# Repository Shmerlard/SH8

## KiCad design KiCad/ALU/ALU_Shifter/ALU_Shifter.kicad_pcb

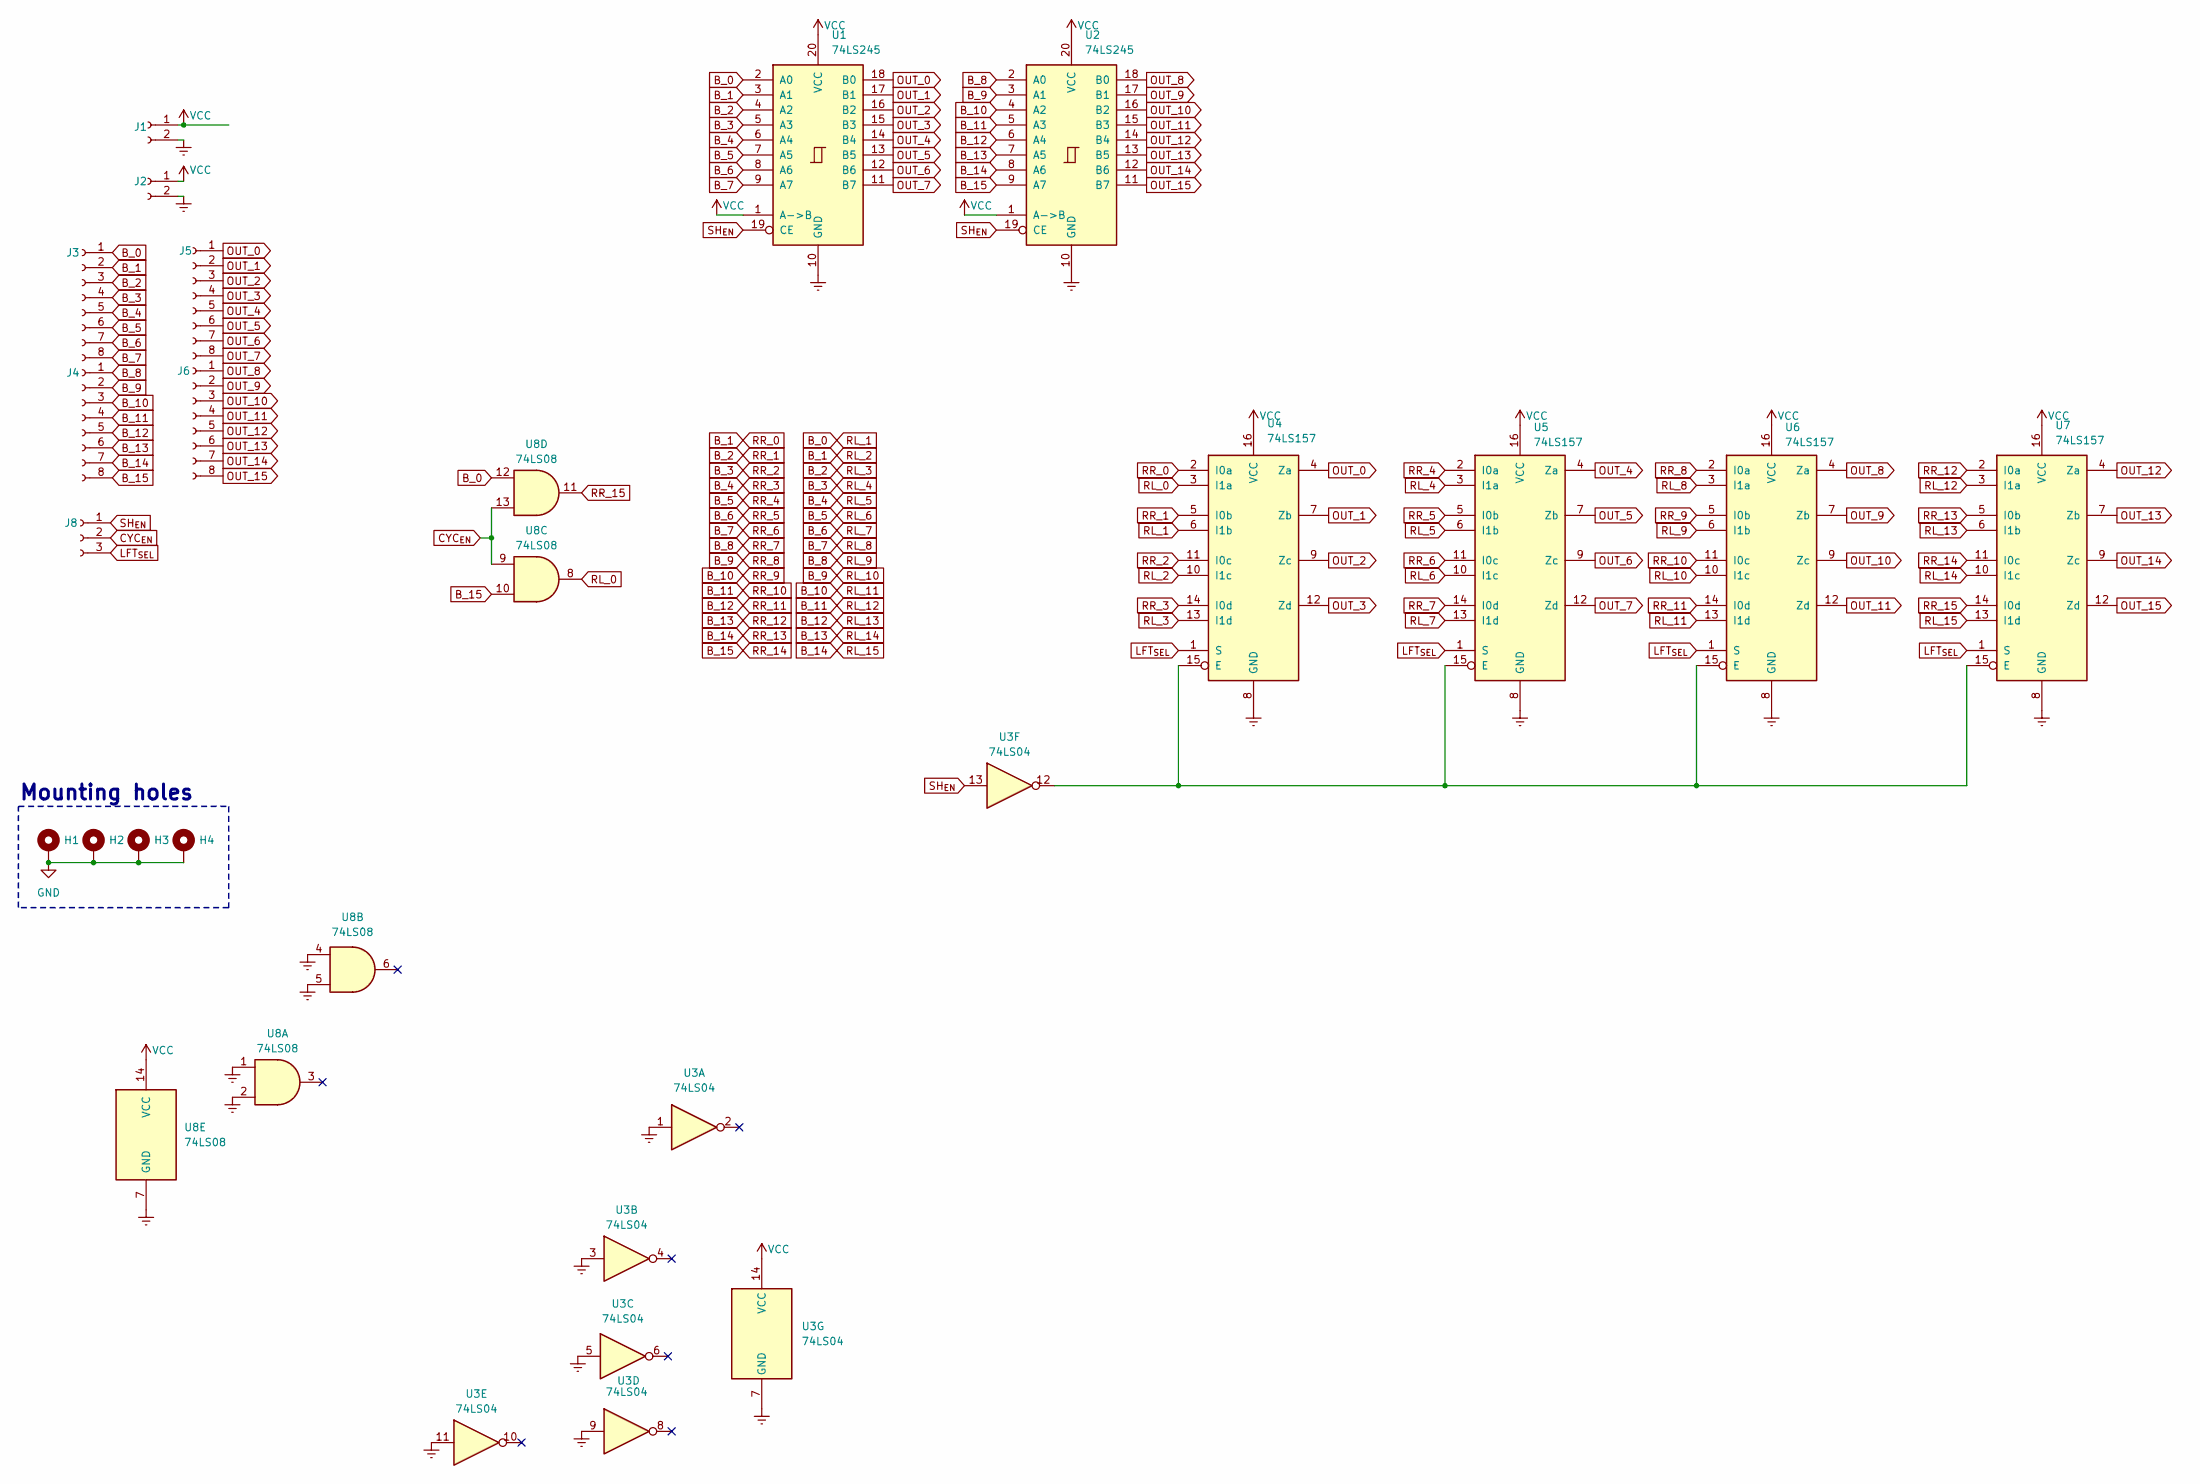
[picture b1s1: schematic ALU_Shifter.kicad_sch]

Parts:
H1, H2, H3, H4: MountingHole_Pad; MountingHole_2.2mm_M2_DIN965_Pad
J1, J2: Conn_01x02_Socket; JST_XH_S2B-XH-A-1_1x02_P2.50mm_Horizontal
J3, J4, J5, J6: Conn_01x08_Socket; jst_xh_s8b_smd
J8: Conn_01x03_Socket; JST_XH_S3B-XH-A-1_1x03_P2.50mm_Horizontal
U1, U2: 74LS245; DIP-20_W7.62mm_Socket_LongPads
U3: 74LS04; DIP-14_W7.62mm_Socket_LongPads
U4, U5, U6, U7: 74LS157; DIP-16_W7.62mm_Socket_LongPads
U8: 74LS08; DIP-14_W7.62mm_Socket_LongPads

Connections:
B_0: J3.1, U1.2 (A0), U4.6 (I1b), U8.12
B_1: J3.2, U1.3 (A1), U4.2 (I0a), U4.10 (I1c)
B_2: J3.3, U1.4 (A2), U4.5 (I0b), U4.13 (I1d)
B_3: J3.4, U1.5 (A3), U4.11 (I0c), U5.3 (I1a)
B_4: J3.5, U1.6 (A4), U4.14 (I0d), U5.6 (I1b)
B_5: J3.6, U1.7 (A5), U5.2 (I0a), U5.10 (I1c)
B_6: J3.7, U1.8 (A6), U5.5 (I0b), U5.13 (I1d)
B_7: J3.8, U1.9 (A7), U5.11 (I0c), U6.3 (I1a)
B_8: J4.1, U2.2 (A0), U5.14 (I0d), U6.6 (I1b)
B_9: J4.2, U2.3 (A1), U6.2 (I0a), U6.10 (I1c)
B_10: J4.3, U2.4 (A2), U6.5 (I0b), U6.13 (I1d)
B_11: J4.4, U2.5 (A3), U6.11 (I0c), U7.3 (I1a)
B_12: J4.5, U2.6 (A4), U6.14 (I0d), U7.6 (I1b)
B_13: J4.6, U2.7 (A5), U7.2 (I0a), U7.10 (I1c)
B_14: J4.7, U2.8 (A6), U7.5 (I0b), U7.13 (I1d)
B_15: J4.8, U2.9 (A7), U7.11 (I0c), U8.10
CYC_{EN}: J8.2, U8.9, U8.13
GND: H1.1, H2.1, H3.1, H4.1, J1.2, J2.2, U1.10 (GND), U2.10 (GND), U3.1, U3.3, U3.5, U3.7 (GND), U3.9, U3.11, U4.8 (GND), U5.8 (GND), U6.8 (GND), U7.8 (GND), U8.1, U8.2, U8.4, U8.5, U8.7 (GND)
LFT_{SEL}: J8.3, U4.1 (S), U5.1 (S), U6.1 (S), U7.1 (S)
unnamed: U3.12, U4.15 (E), U5.15 (E), U6.15 (E), U7.15 (E)
OUT_0: J5.1, U1.18 (B0), U4.4 (Za)
OUT_1: J5.2, U1.17 (B1), U4.7 (Zb)
OUT_2: J5.3, U1.16 (B2), U4.9 (Zc)
OUT_3: J5.4, U1.15 (B3), U4.12 (Zd)
OUT_4: J5.5, U1.14 (B4), U5.4 (Za)
OUT_5: J5.6, U1.13 (B5), U5.7 (Zb)
OUT_6: J5.7, U1.12 (B6), U5.9 (Zc)
OUT_7: J5.8, U1.11 (B7), U5.12 (Zd)
OUT_8: J6.1, U2.18 (B0), U6.4 (Za)
OUT_9: J6.2, U2.17 (B1), U6.7 (Zb)
OUT_10: J6.3, U2.16 (B2), U6.9 (Zc)
OUT_11: J6.4, U2.15 (B3), U6.12 (Zd)
OUT_12: J6.5, U2.14 (B4), U7.4 (Za)
OUT_13: J6.6, U2.13 (B5), U7.7 (Zb)
OUT_14: J6.7, U2.12 (B6), U7.9 (Zc)
OUT_15: J6.8, U2.11 (B7), U7.12 (Zd)
RL_0: U4.3 (I1a), U8.8
RR_15: U7.14 (I0d), U8.11
SH_{EN}: J8.1, U1.19 (CE), U2.19 (CE), U3.13
VCC: J1.1, J2.1, U1.1 (A->B), U1.20 (VCC), U2.1 (A->B), U2.20 (VCC), U3.14 (VCC), U4.16 (VCC), U5.16 (VCC), U6.16 (VCC), U7.16 (VCC), U8.14 (VCC)

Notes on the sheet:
Mounting holes

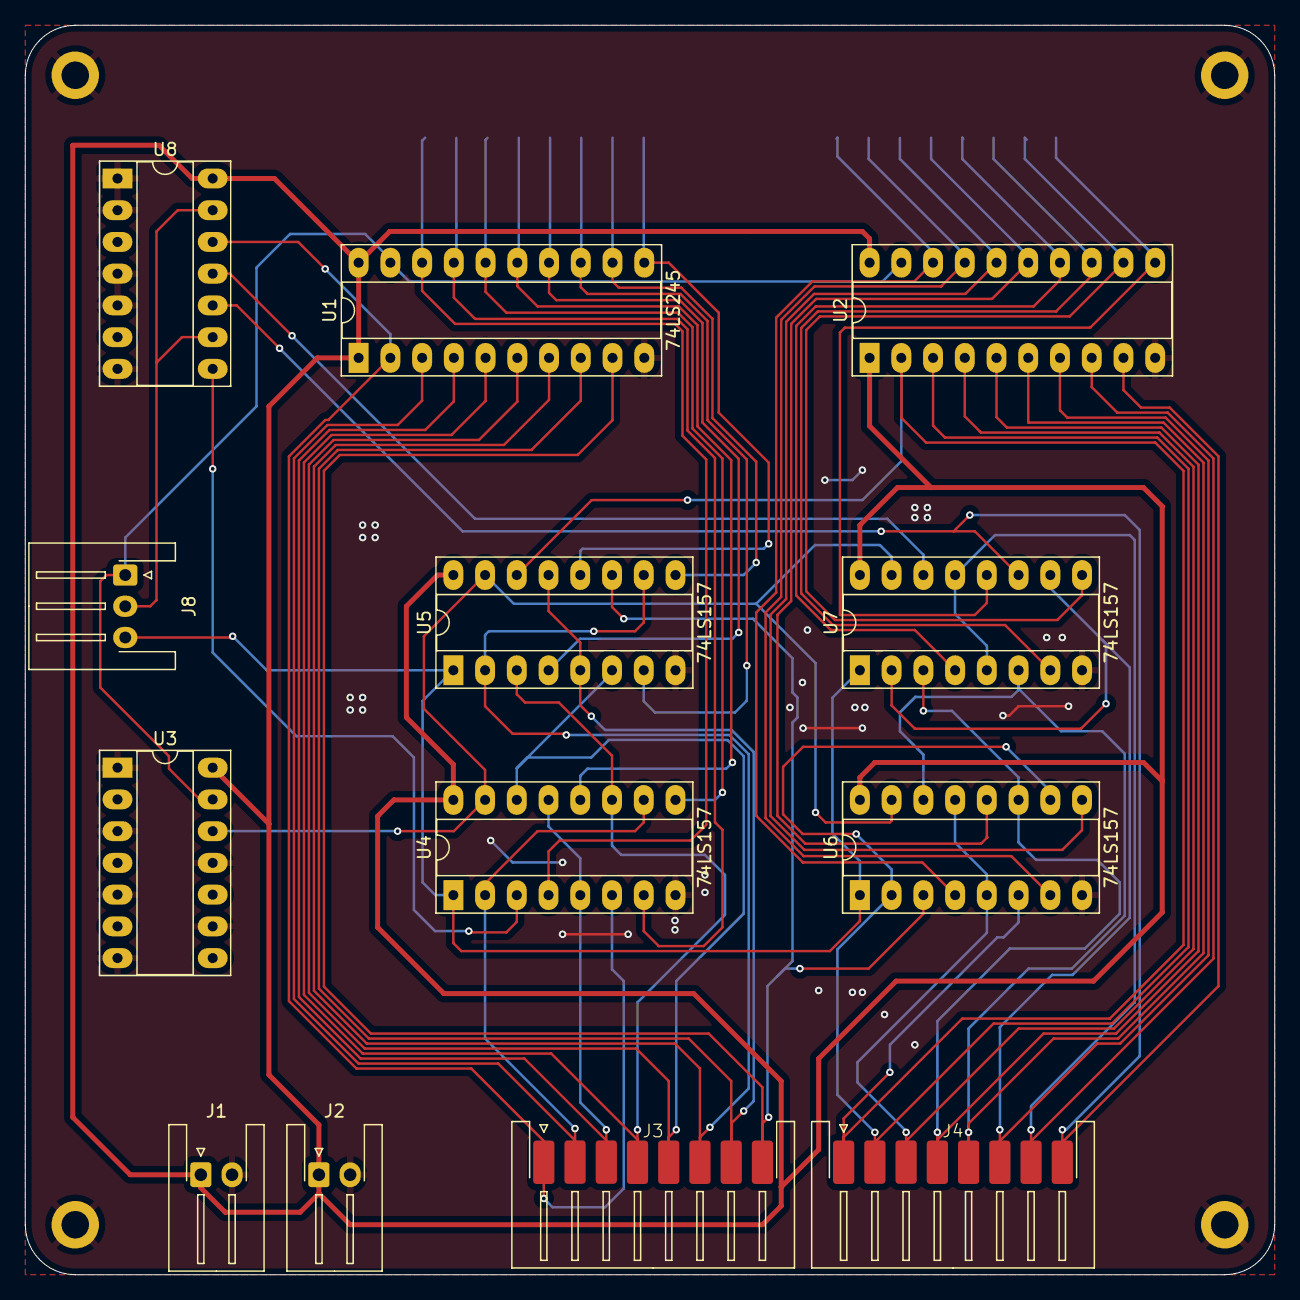
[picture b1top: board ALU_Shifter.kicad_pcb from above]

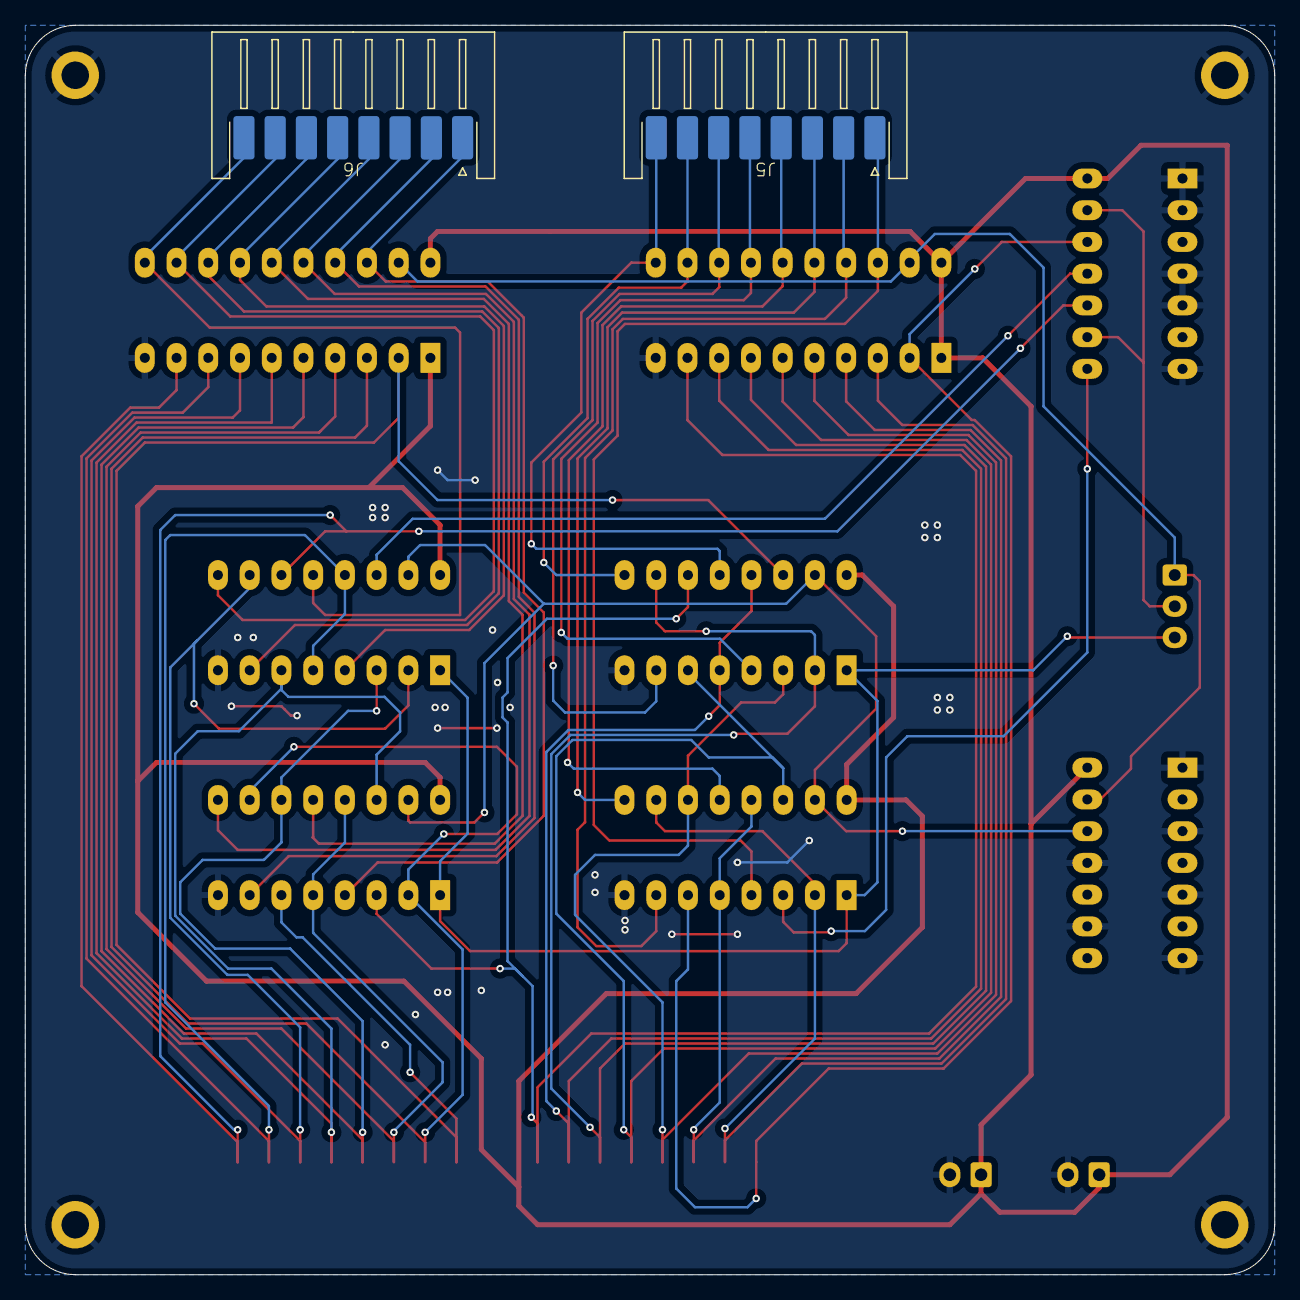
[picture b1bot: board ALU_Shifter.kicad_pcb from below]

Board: 2 copper layers, 100.0 x 100.0 mm, 19 parts (2 on the bottom side), 40 nets.

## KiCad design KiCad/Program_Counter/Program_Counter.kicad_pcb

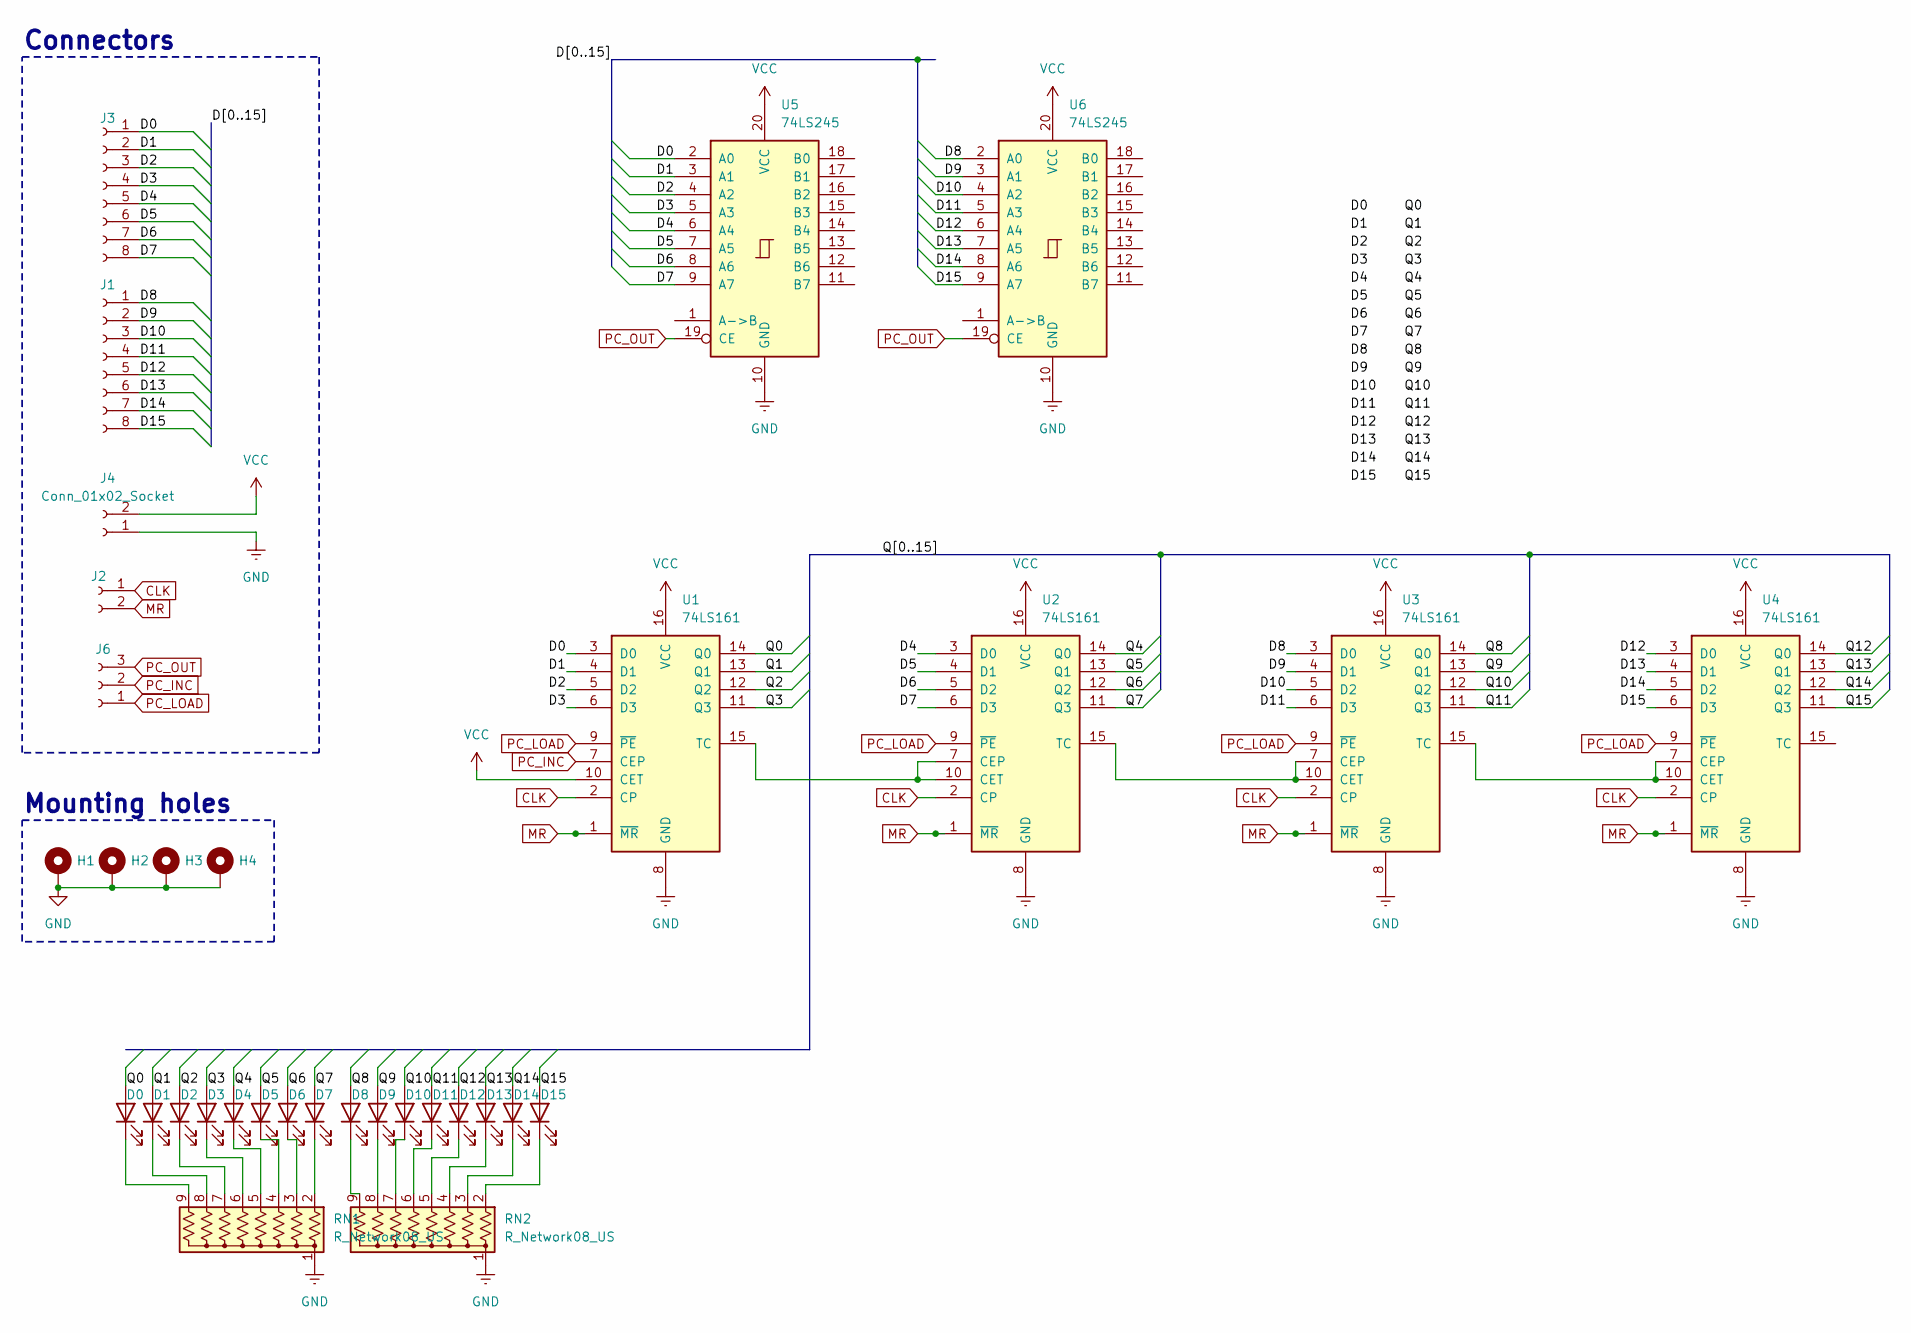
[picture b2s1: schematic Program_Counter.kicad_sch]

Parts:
D0, D1, D2, D3, D4, D5, D6, D7, D8, D9, D10, D11, D12, D13, D14, D15: LED; LED_Rectangular_W3.0mm_H2.0mm
H1, H2, H3, H4: MountingHole_Pad; MountingHole_2.2mm_M2_DIN965_Pad
J1, J3: Conn_01x08_Socket; JST_XH_S8B-XH-A_1x08_P2.50mm_Horizontal
J2, J4: Conn_01x02_Socket; JST_XH_S2B-XH-A_1x02_P2.50mm_Horizontal
J6: Conn_01x03_Socket; JST_XH_S3B-XH-A-1_1x03_P2.50mm_Horizontal
RN1, RN2: R_Network08_US; R_Array_SIP9
U1, U2, U3, U4: 74LS161; DIP-16_W7.62mm_Socket_LongPads
U5, U6: 74LS245; DIP-20_W7.62mm_Socket_LongPads

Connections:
/D0: J3.1, U1.3 (D0), U5.2 (A0)
/D1: J3.2, U1.4 (D1), U5.3 (A1)
/D2: J3.3, U1.5 (D2), U5.4 (A2)
/D3: J3.4, U1.6 (D3), U5.5 (A3)
/D4: J3.5, U2.3 (D0), U5.6 (A4)
/D5: J3.6, U2.4 (D1), U5.7 (A5)
/D6: J3.7, U2.5 (D2), U5.8 (A6)
/D7: J3.8, U2.6 (D3), U5.9 (A7)
/D8: J1.1, U3.3 (D0), U6.2 (A0)
/D9: J1.2, U3.4 (D1), U6.3 (A1)
/D10: J1.3, U3.5 (D2), U6.4 (A2)
/D11: J1.4, U3.6 (D3), U6.5 (A3)
/D12: J1.5, U4.3 (D0), U6.6 (A4)
/D13: J1.6, U4.4 (D1), U6.7 (A5)
/D14: J1.7, U4.5 (D2), U6.8 (A6)
/D15: J1.8, U4.6 (D3), U6.9 (A7)
/Q0: D0.2 (A), U1.14 (Q0)
/Q1: D1.2 (A), U1.13 (Q1)
/Q2: D2.2 (A), U1.12 (Q2)
/Q3: D3.2 (A), U1.11 (Q3)
/Q4: D4.2 (A), U2.14 (Q0)
/Q5: D5.2 (A), U2.13 (Q1)
/Q6: D6.2 (A), U2.12 (Q2)
/Q7: D7.2 (A), U2.11 (Q3)
/Q8: D8.2 (A), U3.14 (Q0)
/Q9: D9.2 (A), U3.13 (Q1)
/Q10: D10.2 (A), U3.12 (Q2)
/Q11: D11.2 (A), U3.11 (Q3)
/Q12: D12.2 (A), U4.14 (Q0)
/Q13: D13.2 (A), U4.13 (Q1)
/Q14: D14.2 (A), U4.12 (Q2)
/Q15: D15.2 (A), U4.11 (Q3)
CLK: J2.1, U1.2 (CP), U2.2 (CP), U3.2 (CP), U4.2 (CP); also elsewhere on the board
GND: H1.1, H2.1, H3.1, H4.1, J4.1, RN1.1 (common), RN2.1 (common), U1.8 (GND), U2.8 (GND), U3.8 (GND), U4.8 (GND), U5.10 (GND), U6.10 (GND)
MR: J2.2, U1.1 (~MR), U2.1 (~MR), U3.1 (~MR), U4.1 (~MR); also elsewhere on the board
unnamed: D0.1 (K), RN1.9 (R8)
unnamed: D1.1 (K), RN1.8 (R7)
unnamed: D2.1 (K), RN1.7 (R6)
unnamed: D3.1 (K), RN1.6 (R5)
unnamed: D4.1 (K), RN1.5 (R4)
unnamed: D5.1 (K), RN1.4 (R3)
unnamed: D6.1 (K), RN1.3 (R2)
unnamed: D7.1 (K), RN1.2 (R1)
unnamed: D8.1 (K), RN2.9 (R8)
unnamed: D9.1 (K), RN2.8 (R7)
unnamed: D10.1 (K), RN2.7 (R6)
unnamed: D11.1 (K), RN2.6 (R5)
unnamed: D12.1 (K), RN2.5 (R4)
unnamed: D13.1 (K), RN2.4 (R3)
unnamed: D14.1 (K), RN2.3 (R2)
unnamed: D15.1 (K), RN2.2 (R1)
unnamed: U1.15 (TC), U2.7 (CEP), U2.10 (CET)
unnamed: U2.15 (TC), U3.7 (CEP), U3.10 (CET)
unnamed: U3.15 (TC), U4.7 (CEP), U4.10 (CET)
PC_INC: J6.2, U1.7 (CEP)
PC_LOAD: J6.1, U1.9 (~PE), U2.9 (~PE), U3.9 (~PE), U4.9 (~PE)
PC_OUT: J6.3, U5.19 (CE), U6.19 (CE)
VCC: J4.2, U1.10 (CET), U1.16 (VCC), U2.16 (VCC), U3.16 (VCC), U4.16 (VCC), U5.20 (VCC), U6.20 (VCC)

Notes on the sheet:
Mounting holes
Connectors

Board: 2 copper layers, 34 parts (0 on the bottom side), 58 nets, no tracks yet.

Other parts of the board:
J5: Conn_01x02_Socket; JST_XH_S2B-XH-A_1x02_P2.50mm_Horizontal

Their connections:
CLK: J5.2; also elsewhere on the board
MR: J5.1; also elsewhere on the board

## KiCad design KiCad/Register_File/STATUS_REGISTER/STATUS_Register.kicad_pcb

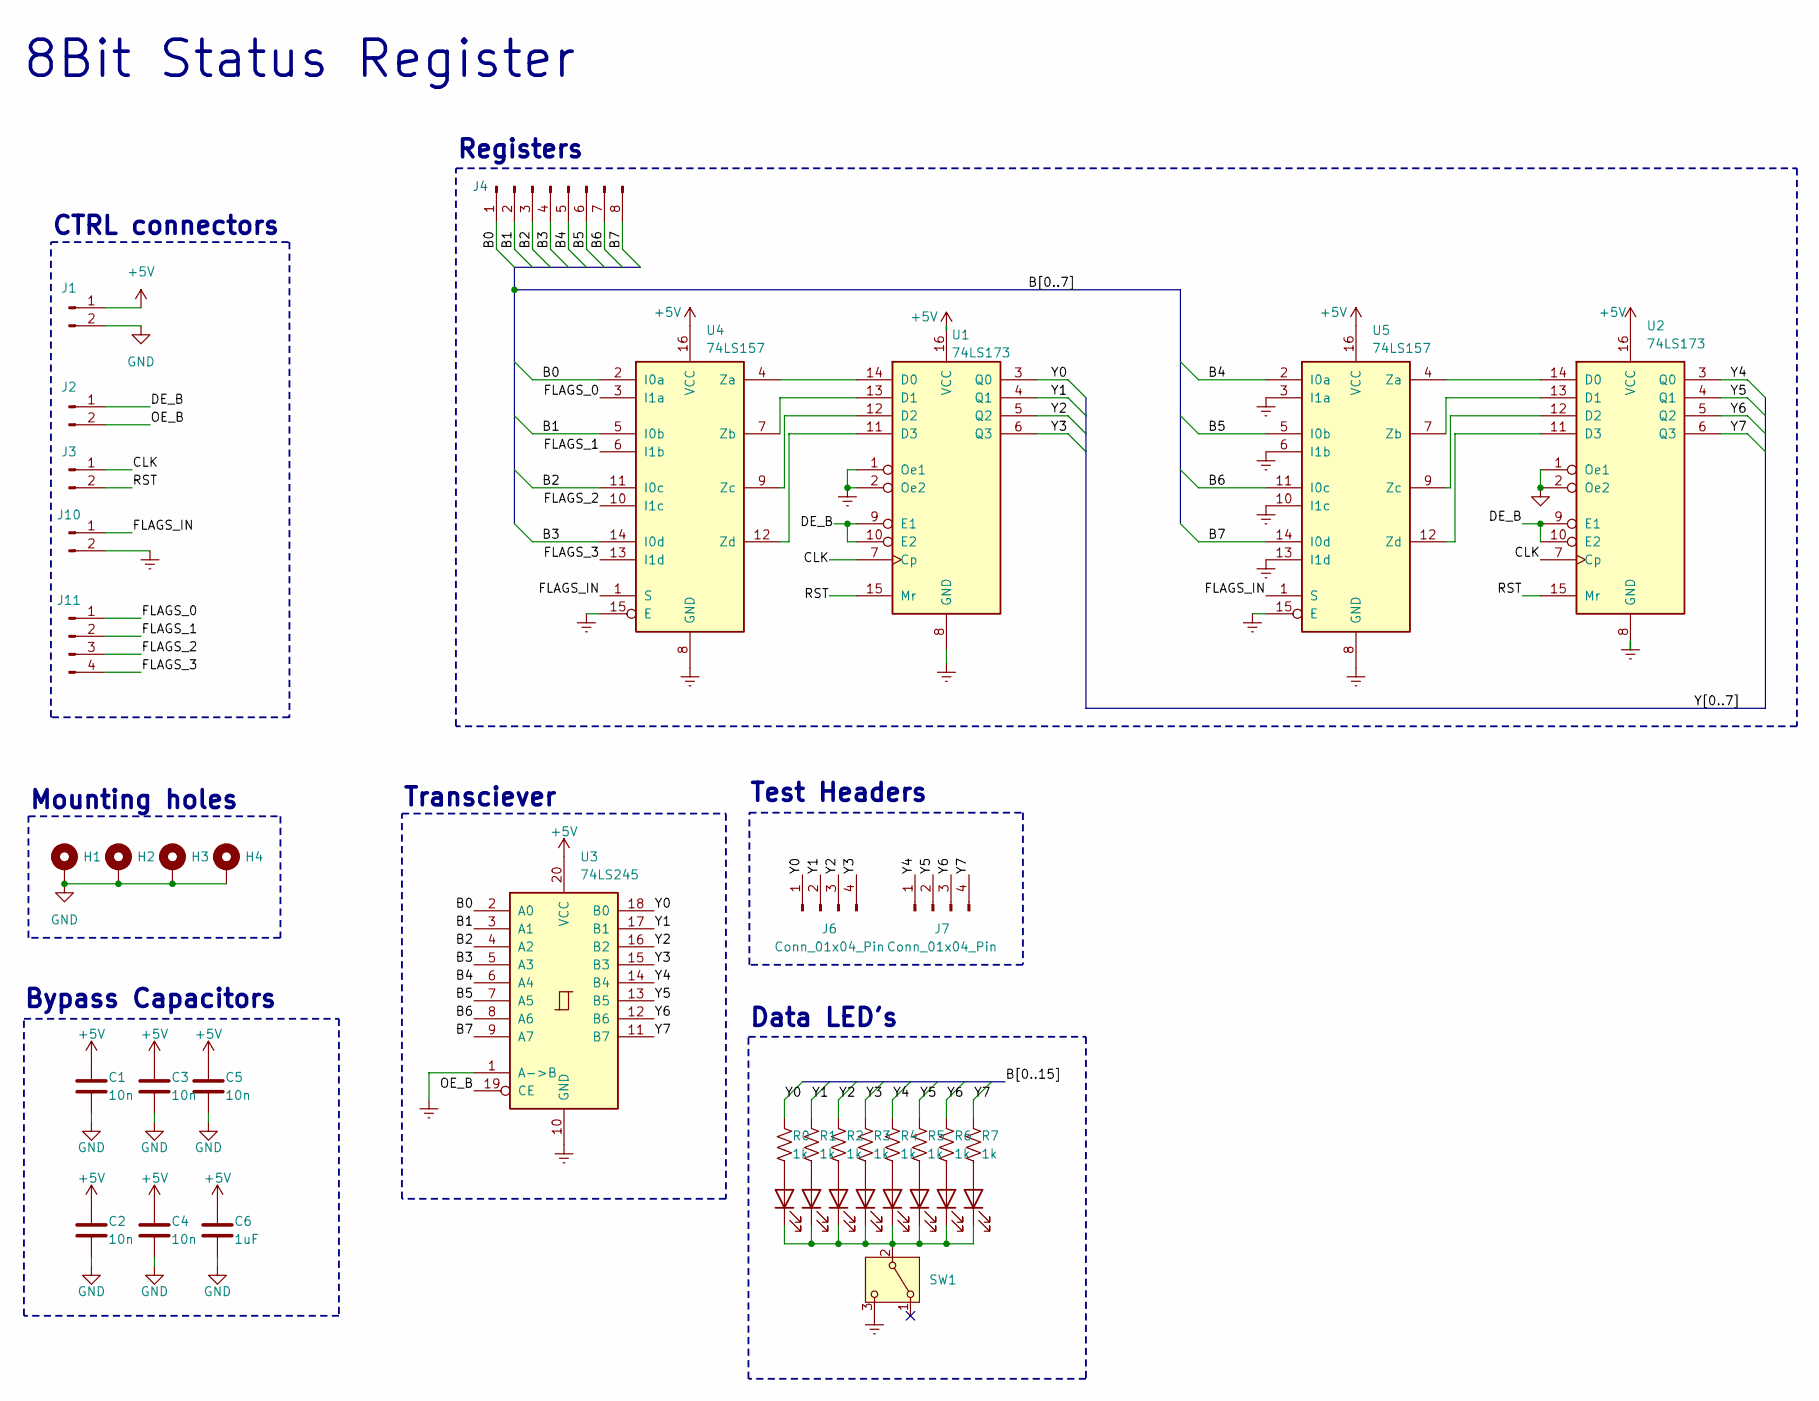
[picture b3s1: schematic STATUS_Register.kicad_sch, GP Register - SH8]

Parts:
C1, C2, C3, C4, C5: 10n; C_Disc_D3.8mm_W2.6mm_P2.50mm
C6: 1uF; C_Radial_D6.3mm_H11.0mm_P2.50mm
D1, D2, D3, D4, D5, D6, D7, D8: LED; LED_Rectangular_W3.0mm_H2.0mm
H1, H2, H3, H4: MountingHole_Pad; MountingHole_2.2mm_M2_DIN965_Pad
J1, J2, J3, J10: Conn_01x02_Pin; JST_XH_S2B-XH-A-1_1x02_P2.50mm_Horizontal
J4: Conn_01x08_Pin; JST_XH_S8B-XH-A-1_1x08_P2.50mm_Horizontal
J6, J7: Conn_01x04_Pin; PinHeader_1x04_P2.54mm_Vertical
J11: Conn_01x04_Pin; JST_XH_S4B-XH-A-1_1x04_P2.50mm_Horizontal
R0, R1, R2, R3, R4, R5, R6, R7: 1k; R_Axial_DIN0204_L3.6mm_D1.6mm_P7.62mm_Horizontal
SW1: SW_SPDT; SW_Slide_SPDT_Angled_CK_OS102011MA1Q
U1, U2: 74LS173; DIP-16_W7.62mm_Socket_LongPads
U3: 74LS245; DIP-20_W7.62mm_Socket_LongPads
U4, U5: 74LS157; DIP-16_W7.62mm_Socket_LongPads

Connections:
+5V: C1.1, C2.1, C3.1, C4.1, C5.1, C6.1, J1.1, U1.16 (VCC), U2.16 (VCC), U3.20 (VCC), U4.16 (VCC), U5.16 (VCC)
/B0: J4.1, U3.2 (A0), U4.2 (I0a)
/B1: J4.2, U3.3 (A1), U4.5 (I0b)
/B2: J4.3, U3.4 (A2), U4.11 (I0c)
/B3: J4.4, U3.5 (A3), U4.14 (I0d)
/B4: J4.5, U3.6 (A4), U5.2 (I0a)
/B5: J4.6, U3.7 (A5), U5.5 (I0b)
/B6: J4.7, U3.8 (A6), U5.11 (I0c)
/B7: J4.8, U3.9 (A7), U5.14 (I0d)
/CLK: J3.1, U1.7 (Cp), U2.7 (Cp)
/DE_B: J2.1, U1.9 (E1), U1.10 (E2), U2.9 (E1), U2.10 (E2)
/FLAGS_0: J11.1, U4.3 (I1a)
/FLAGS_1: J11.2, U4.6 (I1b)
/FLAGS_2: J11.3, U4.10 (I1c)
/FLAGS_3: J11.4, U4.13 (I1d)
/FLAGS_IN: J10.1, U4.1 (S), U5.1 (S)
/OE_B: J2.2, U3.19 (CE)
/RST: J3.2, U1.15 (Mr), U2.15 (Mr)
/Y0: J6.1, R0.1, U1.3 (Q0), U3.18 (B0)
/Y1: J6.2, R1.1, U1.4 (Q1), U3.17 (B1)
/Y2: J6.3, R2.1, U1.5 (Q2), U3.16 (B2)
/Y3: J6.4, R3.1, U1.6 (Q3), U3.15 (B3)
/Y4: J7.1, R4.1, U2.3 (Q0), U3.14 (B4)
/Y5: J7.2, R5.1, U2.4 (Q1), U3.13 (B5)
/Y6: J7.3, R6.1, U2.5 (Q2), U3.12 (B6)
/Y7: J7.4, R7.1, U2.6 (Q3), U3.11 (B7)
GND: C1.2, C2.2, C3.2, C4.2, C5.2, C6.2, H1.1, H2.1, H3.1, H4.1, J1.2, J10.2, SW1.3 (C), U1.1 (Oe1), U1.2 (Oe2), U1.8 (GND), U2.1 (Oe1), U2.2 (Oe2), U2.8 (GND), U3.1 (A->B), U3.10 (GND), U4.8 (GND), U4.15 (E), U5.3 (I1a), U5.6 (I1b), U5.8 (GND), U5.10 (I1c), U5.13 (I1d), U5.15 (E)
unnamed: D1.2 (A), R0.2
unnamed: D1.1 (K), D2.1 (K), D3.1 (K), D4.1 (K), D5.1 (K), D6.1 (K), D7.1 (K), D8.1 (K), SW1.2 (B)
unnamed: D2.2 (A), R1.2
unnamed: D3.2 (A), R2.2
unnamed: D4.2 (A), R3.2
unnamed: D5.2 (A), R4.2
unnamed: D6.2 (A), R5.2
unnamed: D7.2 (A), R6.2
unnamed: D8.2 (A), R7.2
unnamed: U1.14 (D0), U4.4 (Za)
unnamed: U1.13 (D1), U4.7 (Zb)
unnamed: U1.12 (D2), U4.9 (Zc)
unnamed: U1.11 (D3), U4.12 (Zd)
unnamed: U2.14 (D0), U5.4 (Za)
unnamed: U2.13 (D1), U5.7 (Zb)
unnamed: U2.12 (D2), U5.9 (Zc)
unnamed: U2.11 (D3), U5.12 (Zd)

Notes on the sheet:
8Bit Status Register
Data LED's
Bypass Capacitors
Registers
Mounting holes
Test Headers
CTRL connectors
Transciever

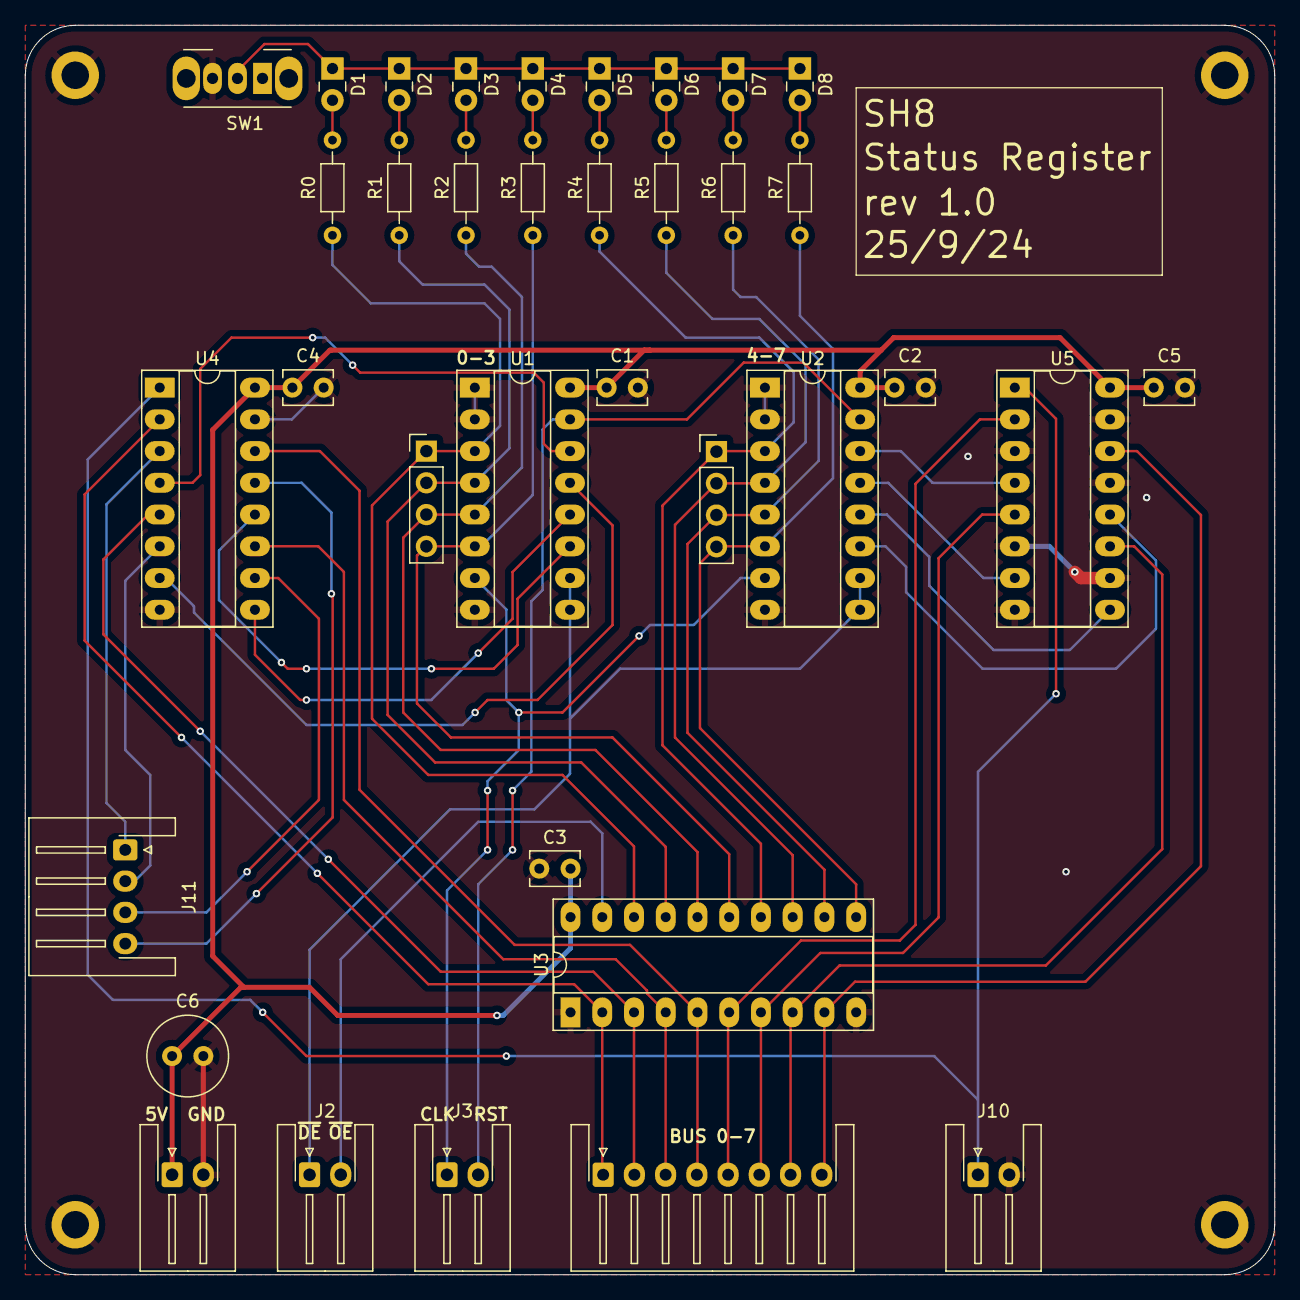
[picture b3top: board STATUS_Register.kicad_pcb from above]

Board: 2 copper layers, 100.0 x 100.0 mm, 40 parts (0 on the bottom side), 44 nets.

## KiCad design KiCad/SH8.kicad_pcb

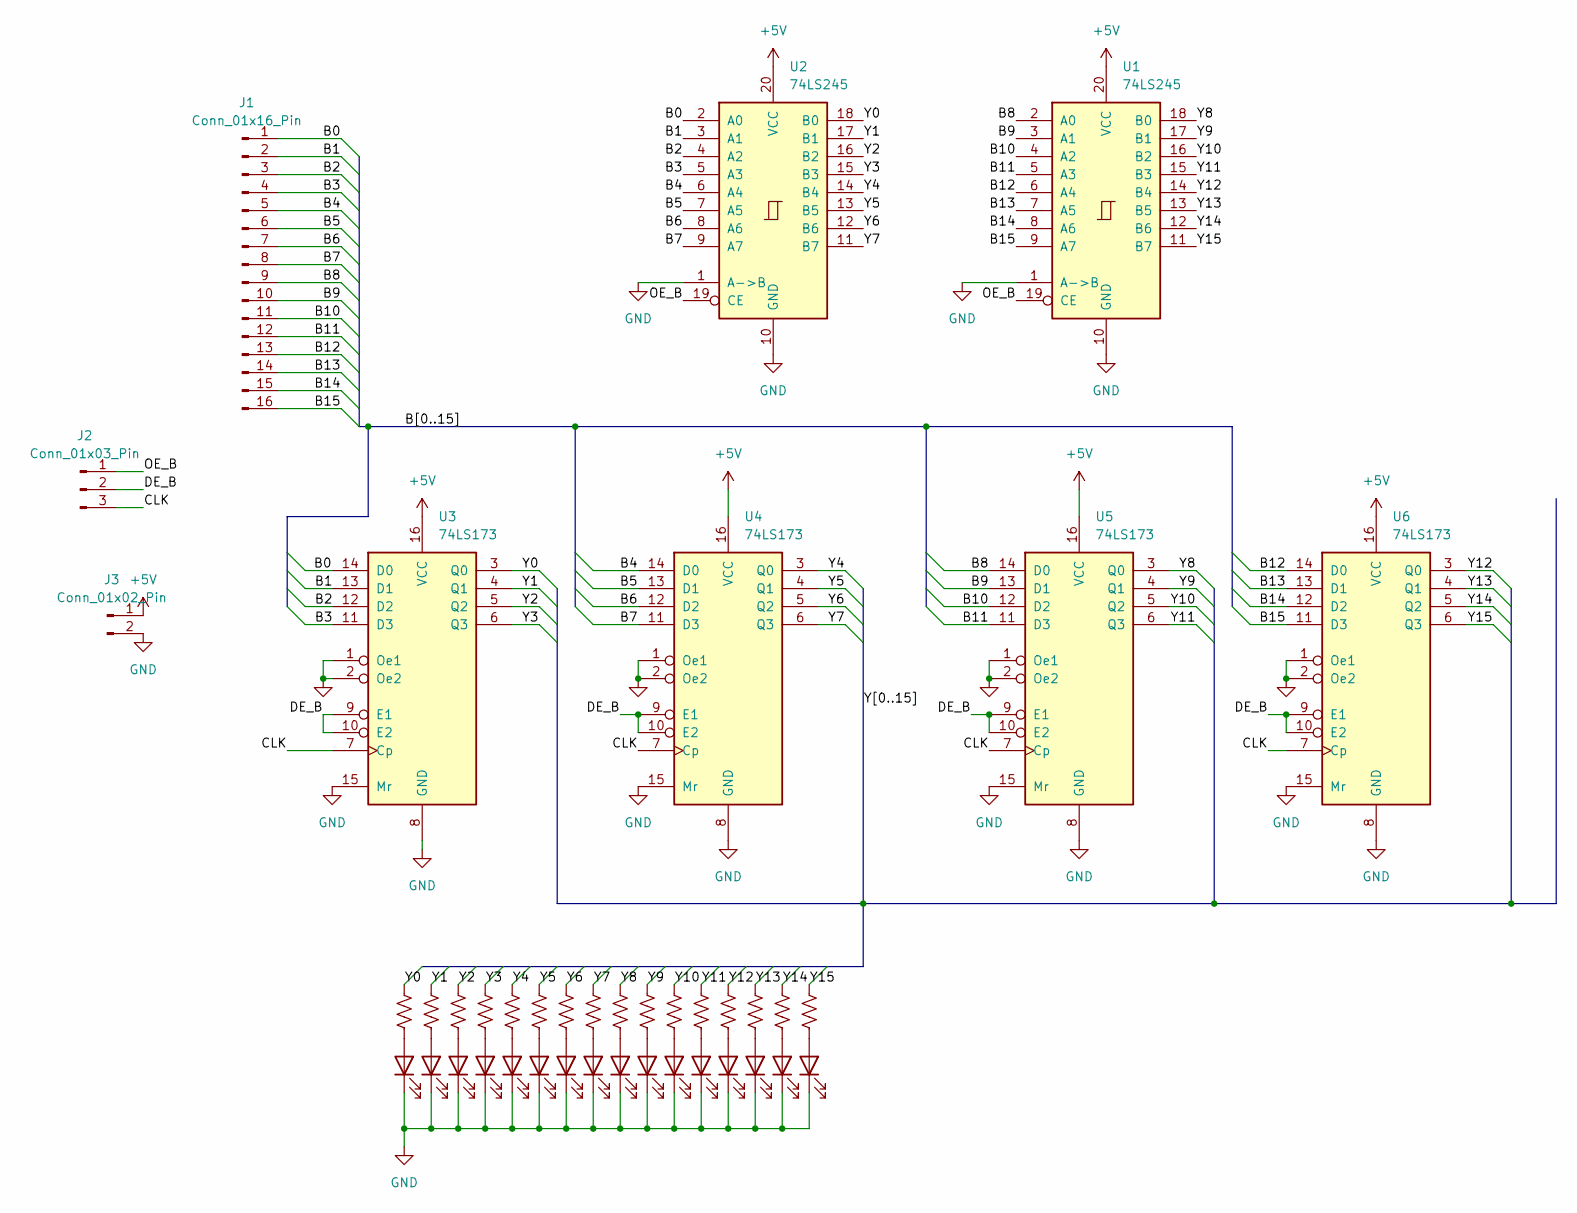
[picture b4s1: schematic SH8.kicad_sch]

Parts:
D1, D2, D3, D4, D5, D6, D7, D8, D9, D10, D11, D12, D13, D14, D15, D16: LED; LED_Rectangular_W3.0mm_H2.0mm
J1: Conn_01x16_Pin; JST_XH_S16B-XH-A_1x16_P2.50mm_Horizontal
J2: Conn_01x03_Pin; JST_XH_S3B-XH-A_1x03_P2.50mm_Horizontal
J3: Conn_01x02_Pin; JST_XH_S2B-XH-A_1x02_P2.50mm_Horizontal
R1, R2, R3, R4, R5, R6, R7, R8, R9, R10, R11, R12, R13, R14, R15, R16: 220; R_Axial_DIN0204_L3.6mm_D1.6mm_P5.08mm_Horizontal
U1, U2: 74LS245; DIP-20_W7.62mm
U3, U4, U5, U6: 74LS173; DIP-16_W7.62mm

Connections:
+5V: J3.1, U1.20 (VCC), U2.20 (VCC), U3.16 (VCC), U4.16 (VCC), U5.16 (VCC), U6.16 (VCC)
/B0: J1.1, U2.2 (A0), U3.14 (D0)
/B1: J1.2, U2.3 (A1), U3.13 (D1)
/B2: J1.3, U2.4 (A2), U3.12 (D2)
/B3: J1.4, U2.5 (A3), U3.11 (D3)
/B4: J1.5, U2.6 (A4), U4.14 (D0)
/B5: J1.6, U2.7 (A5), U4.13 (D1)
/B6: J1.7, U2.8 (A6), U4.12 (D2)
/B7: J1.8, U2.9 (A7), U4.11 (D3)
/B8: J1.9, U1.2 (A0), U5.14 (D0)
/B9: J1.10, U1.3 (A1), U5.13 (D1)
/B10: J1.11, U1.4 (A2), U5.12 (D2)
/B11: J1.12, U1.5 (A3), U5.11 (D3)
/B12: J1.13, U1.6 (A4), U6.14 (D0)
/B13: J1.14, U1.7 (A5), U6.13 (D1)
/B14: J1.15, U1.8 (A6), U6.12 (D2)
/B15: J1.16, U1.9 (A7), U6.11 (D3)
/CLK: J2.3, U3.7 (Cp), U4.7 (Cp), U5.7 (Cp), U6.7 (Cp)
/DE_B: J2.2, U3.9 (E1), U3.10 (E2), U4.9 (E1), U4.10 (E2), U5.9 (E1), U5.10 (E2), U6.9 (E1), U6.10 (E2)
/OE_B: J2.1, U1.19 (CE), U2.19 (CE)
/Y0: R1.1, U2.18 (B0), U3.3 (Q0)
/Y1: R2.1, U2.17 (B1), U3.4 (Q1)
/Y2: R3.1, U2.16 (B2), U3.5 (Q2)
/Y3: R4.1, U2.15 (B3), U3.6 (Q3)
/Y4: R5.1, U2.14 (B4), U4.3 (Q0)
/Y5: R6.1, U2.13 (B5), U4.4 (Q1)
/Y6: R7.1, U2.12 (B6), U4.5 (Q2)
/Y7: R8.1, U2.11 (B7), U4.6 (Q3)
/Y8: R9.1, U1.18 (B0), U5.3 (Q0)
/Y9: R10.1, U1.17 (B1), U5.4 (Q1)
/Y10: R11.1, U1.16 (B2), U5.5 (Q2)
/Y11: R12.1, U1.15 (B3), U5.6 (Q3)
/Y12: R13.1, U1.14 (B4), U6.3 (Q0)
/Y13: R14.1, U1.13 (B5), U6.4 (Q1)
/Y14: R15.1, U1.12 (B6), U6.5 (Q2)
/Y15: R16.1, U1.11 (B7), U6.6 (Q3)
GND: D1.1 (K), D2.1 (K), D3.1 (K), D4.1 (K), D5.1 (K), D6.1 (K), D7.1 (K), D8.1 (K), D9.1 (K), D10.1 (K), D11.1 (K), D12.1 (K), D13.1 (K), D14.1 (K), D15.1 (K), D16.1 (K), J3.2, U1.1 (A->B), U1.10 (GND), U2.1 (A->B), U2.10 (GND), U3.1 (Oe1), U3.2 (Oe2), U3.8 (GND), U3.15 (Mr), U4.1 (Oe1), U4.2 (Oe2), U4.8 (GND), U4.15 (Mr), U5.1 (Oe1), U5.2 (Oe2), U5.8 (GND), U5.15 (Mr), U6.1 (Oe1), U6.2 (Oe2), U6.8 (GND), U6.15 (Mr)
unnamed: D1.2 (A), R1.2
unnamed: D2.2 (A), R2.2
unnamed: D3.2 (A), R3.2
unnamed: D4.2 (A), R4.2
unnamed: D5.2 (A), R5.2
unnamed: D6.2 (A), R6.2
unnamed: D7.2 (A), R7.2
unnamed: D8.2 (A), R8.2
unnamed: D9.2 (A), R9.2
unnamed: D10.2 (A), R10.2
unnamed: D11.2 (A), R11.2
unnamed: D12.2 (A), R12.2
unnamed: D13.2 (A), R13.2
unnamed: D14.2 (A), R14.2
unnamed: D15.2 (A), R15.2
unnamed: D16.2 (A), R16.2
